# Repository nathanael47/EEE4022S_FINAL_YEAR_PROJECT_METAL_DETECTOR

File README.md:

# EEE4022S_FINAL_YEAR_PROJECT_METAL_DETECTOR
This is the git repository for all code my design and implementation of a metal detector

# PROJECT NAME: DESIGN AND IMPLEMENTATION OF A METAL DETECTOR

# DESCRIPTION:
This is the design and implementation of a metal detector that can detect metals and distinguish if it is ferrous or non ferrous

# INSTALLATION
1. Download the zip version of the repository.
2. Alternatively, pull the repository using the following line;

# USAGE
Prototype:
1. Install arduino and teensyduino
2. Run any of the implementations.
3. Run Metal_Detector.ino

# CREDITS: Done by NATHANAEL GEORGE THOMAS-5/11/2022

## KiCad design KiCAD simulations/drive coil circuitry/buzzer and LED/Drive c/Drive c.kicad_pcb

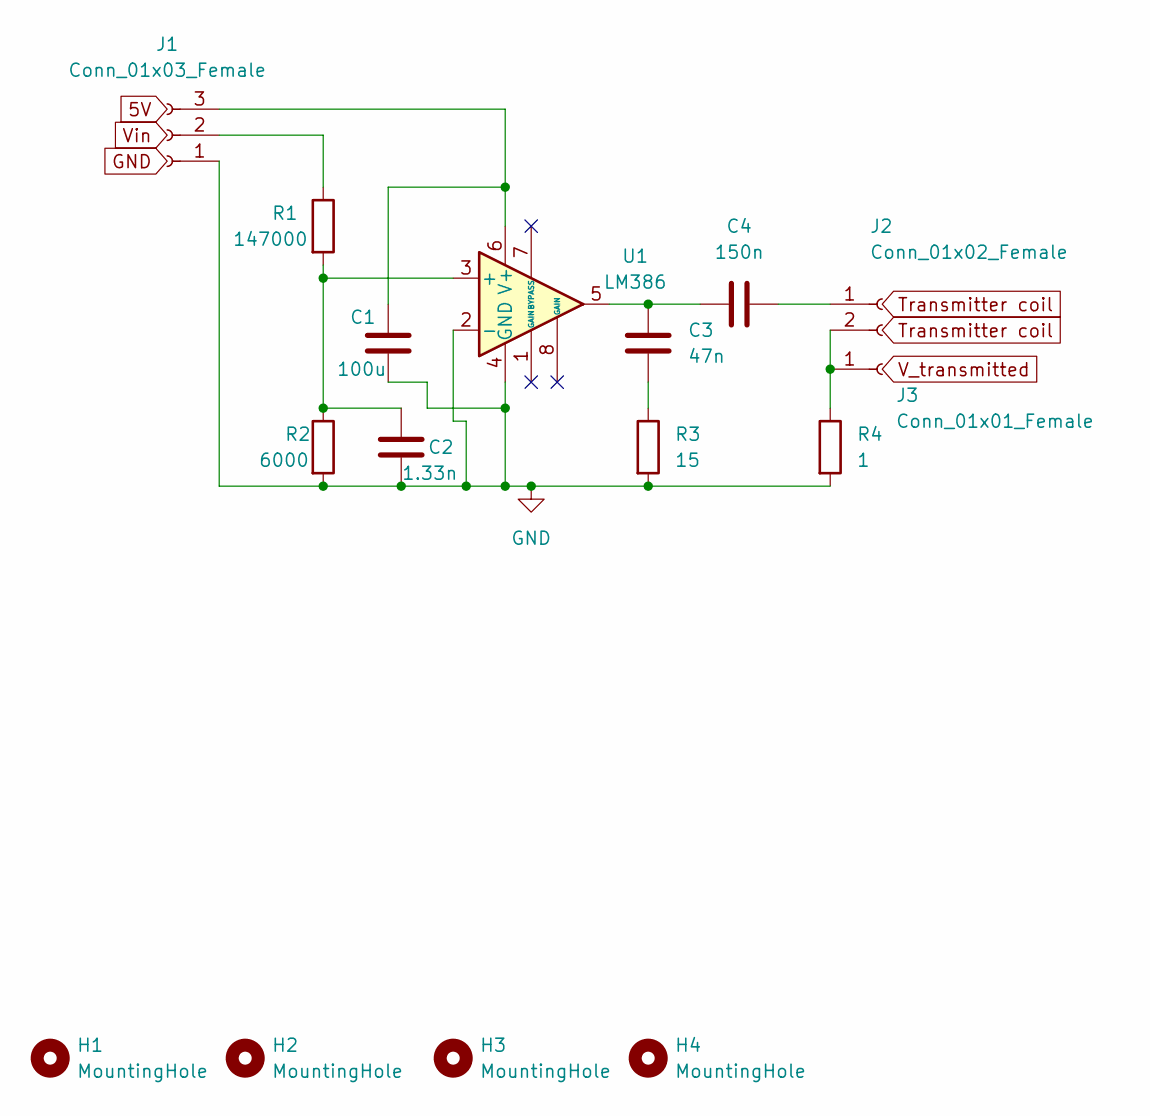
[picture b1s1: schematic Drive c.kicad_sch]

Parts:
C1: 100u; CP_Radial_D7.5mm_P2.50mm
C2: 1.33n; CP_Radial_D7.5mm_P2.50mm
C3: 47n; CP_Radial_D7.5mm_P2.50mm
C4: 150n; CP_Radial_D7.5mm_P2.50mm
H1, H2, H3, H4: MountingHole; MountingHole_2.7mm_M2.5_ISO14580_Pad_TopOnly
J1: Conn_01x03_Female; PinSocket_1x03_P2.54mm_Vertical
J2: Conn_01x02_Female; PinSocket_1x02_P2.54mm_Vertical
J3: Conn_01x01_Female; PinSocket_1x01_P2.54mm_Vertical
R1: 147000; R_Axial_DIN0309_L9.0mm_D3.2mm_P12.70mm_Horizontal
R2: 6000; R_Axial_DIN0309_L9.0mm_D3.2mm_P12.70mm_Horizontal
R3: 15; R_Axial_DIN0309_L9.0mm_D3.2mm_P12.70mm_Horizontal
R4: 1; R_Axial_DIN0309_L9.0mm_D3.2mm_P12.70mm_Horizontal
U1: LM386; DIP-8_W7.62mm

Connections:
GND: C1.2, C2.2, J1.1, R2.2, R3.2, R4.2, U1.2 (-), U1.4 (GND)
unnamed: C1.1, J1.3, U1.6 (V+)
unnamed: C2.1, R1.2, R2.1, U1.3 (+)
unnamed: C3.1, R3.1
unnamed: C3.2, C4.1, U1.5
unnamed: C4.2, J2.1
unnamed: J1.2, R1.1
unnamed: J2.2, J3.1, R4.1

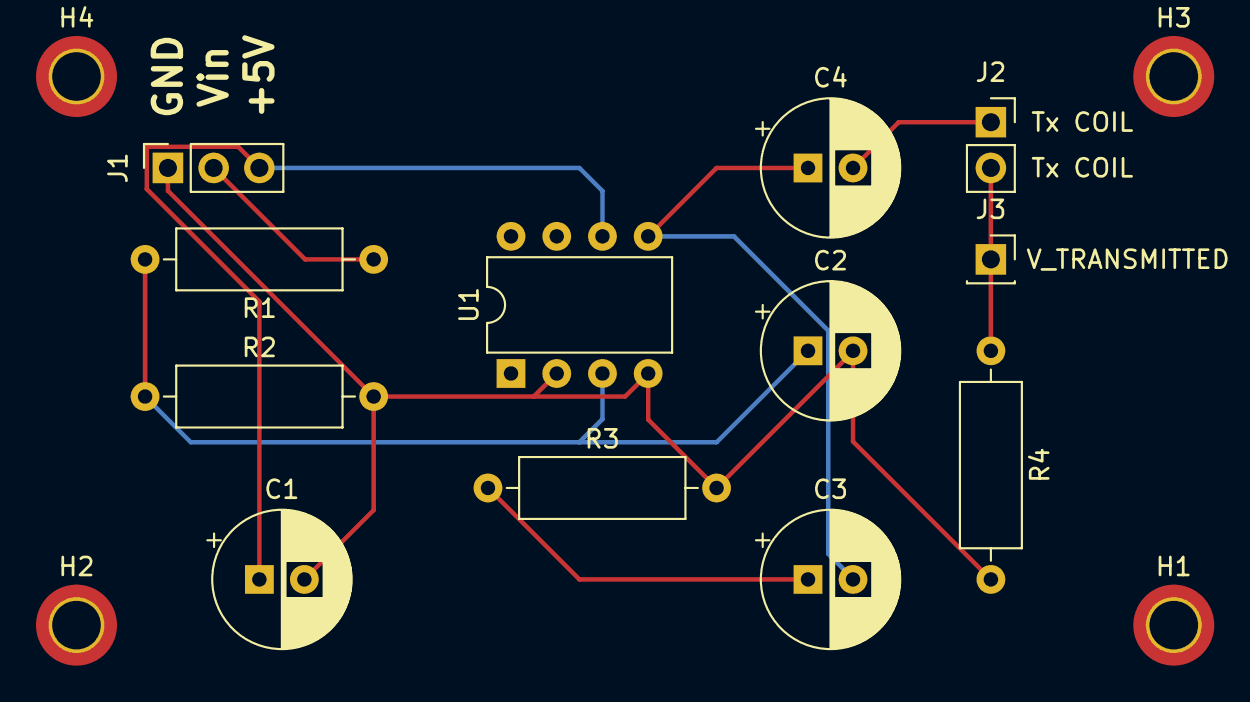
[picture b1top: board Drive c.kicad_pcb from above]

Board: 2 copper layers, 16 parts (0 on the bottom side), 8 nets.

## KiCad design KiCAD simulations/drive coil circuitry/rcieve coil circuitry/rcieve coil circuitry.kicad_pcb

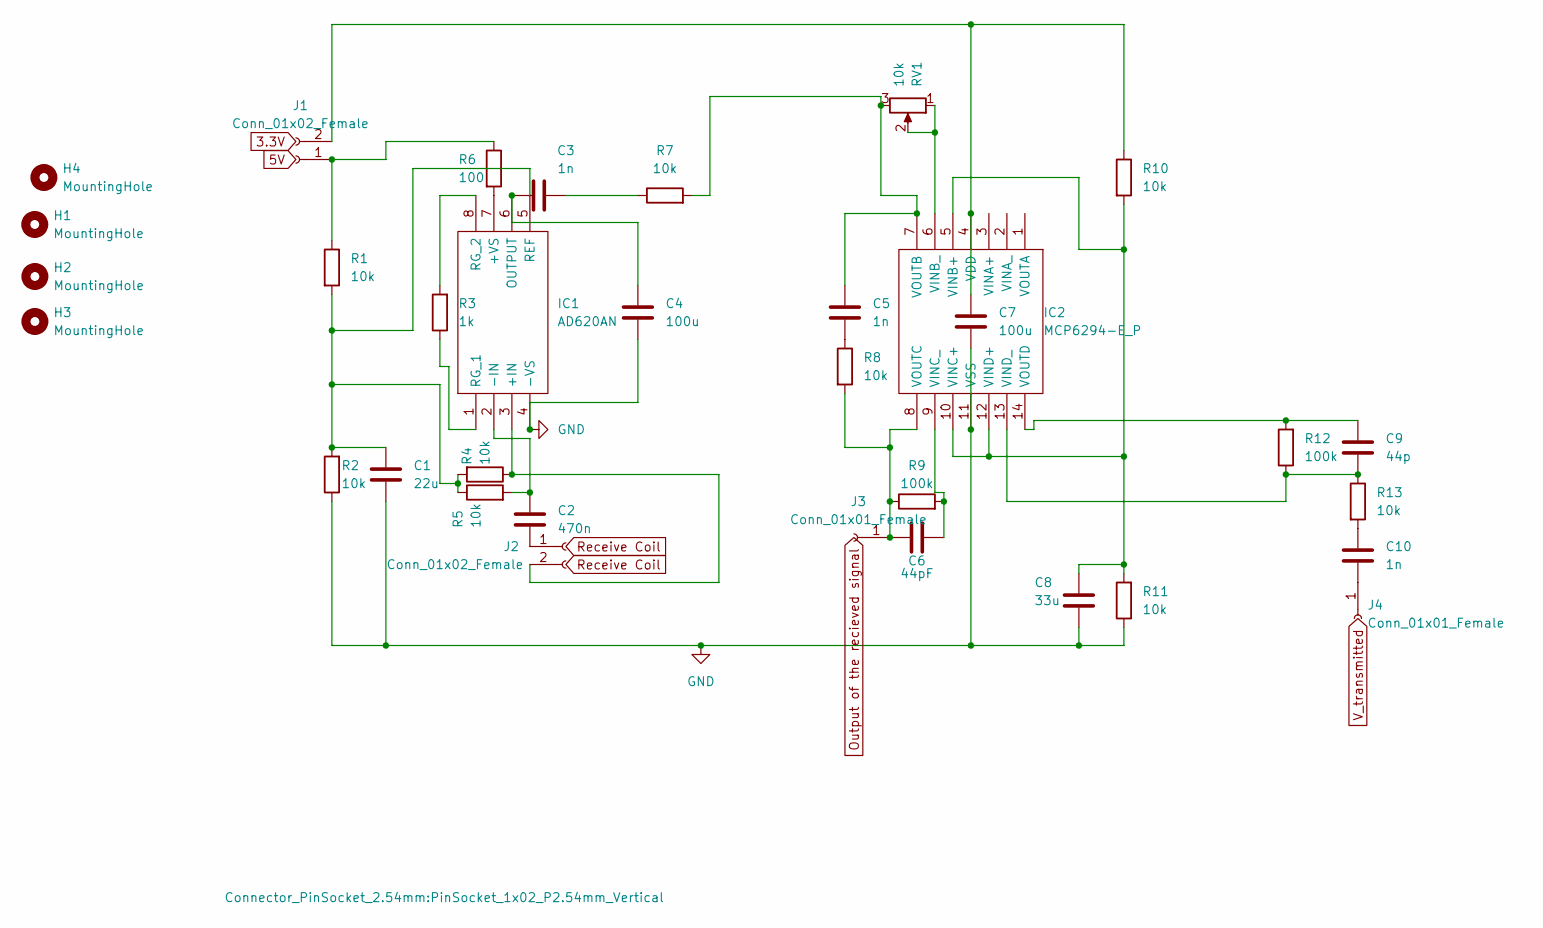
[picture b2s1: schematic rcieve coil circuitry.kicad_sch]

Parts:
C1: 22u; C_Rect_L4.6mm_W3.8mm_P2.50mm_MKS02_FKP02
C2: 470n; C_Rect_L7.0mm_W4.5mm_P5.00mm
C3: 1n; C_Rect_L7.0mm_W6.5mm_P5.00mm
C4: 100u; C_Radial_D10.0mm_H12.5mm_P5.00mm
C5: 1n; C_Rect_L4.6mm_W3.0mm_P2.50mm_MKS02_FKP02
C6: 44pF; C_Rect_L4.6mm_W2.0mm_P2.50mm_MKS02_FKP02
C7: 100u; C_Radial_D6.3mm_H5.0mm_P2.50mm
C8: 33u; C_Radial_D6.3mm_H5.0mm_P2.50mm
C9: 44p; C_Rect_L4.0mm_W2.5mm_P2.50mm
C10: 1n; C_Rect_L4.0mm_W2.5mm_P2.50mm
H1, H2, H3, H4: MountingHole; MountingHole_2.2mm_M2
IC1: AD620AN; DIP-8_W7.62mm_LongPads; Manufacturer_Part_Number AD620AN; Mouser Part Number 584-AD620AN
IC2: MCP6294-E_P; DIP-14_W7.62mm_LongPads; Manufacturer_Part_Number MCP6294-E/P; Mouser Part Number 579-MCP6294-E/P
J1, J2: Conn_01x02_Female; PinSocket_1x02_P2.54mm_Vertical
J3, J4: Conn_01x01_Female; PinSocket_1x01_P2.54mm_Vertical
R1, R2: 10k; R_Axial_DIN0309_L9.0mm_D3.2mm_P5.08mm_Vertical
R3: 1k; R_Axial_DIN0309_L9.0mm_D3.2mm_P5.08mm_Vertical
R4, R5, R7, R8, R10, R11: 10k; R_Axial_DIN0614_L14.3mm_D5.7mm_P15.24mm_Horizontal
R6: 100; R_Axial_DIN0614_L14.3mm_D5.7mm_P15.24mm_Horizontal
R9: 100k; R_Axial_DIN0614_L14.3mm_D5.7mm_P15.24mm_Horizontal
R12: 100k; R_Axial_DIN0414_L11.9mm_D4.5mm_P15.24mm_Horizontal
R13: 10k; R_Axial_DIN0414_L11.9mm_D4.5mm_P15.24mm_Horizontal
RV1: 10k; Potentiometer_Alps_RK09K_Single_Vertical

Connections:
GND: C1.2, C4.2, C7.2, C8.2, IC1.4 (-VS), IC2.11 (VSS), R2.1, R11.1
unnamed: C1.1, IC1.5 (REF), R1.2, R2.2, R4.2, R5.1
unnamed: C2.1, IC1.2 (-IN), R5.2
unnamed: C2.2, J2.1
unnamed: C3.1, C4.1, IC1.6 (OUTPUT)
unnamed: C3.2, R7.1
unnamed: C5.1, IC2.7 (VOUTB), R7.2, RV1.3
unnamed: C5.2, R8.1
unnamed: C6.1, IC2.8 (VOUTC), J3.1, R8.2, R9.1
unnamed: C6.2, IC2.9 (VINC_), R9.2
unnamed: C8.1, IC2.5 (VINB+), IC2.10 (VINC+), IC2.12 (VIND+), R10.2, R11.2
unnamed: C9.1, IC2.14 (VOUTD), R12.2
unnamed: C9.2, IC2.13 (VIND_), R12.1, R13.1
unnamed: C10.1, R13.2
unnamed: C10.2, J4.1
unnamed: IC1.1 (RG_1), R3.1
unnamed: IC1.3 (+IN), J2.2, R4.1
unnamed: IC1.7 (+VS), R6.2
unnamed: IC1.8 (RG_2), R3.2
unnamed: IC2.6 (VINB_), RV1.1, RV1.2
unnamed: J1.1, R1.1, R6.1
unnamed: C7.1, IC2.4 (VDD), J1.2, R10.1

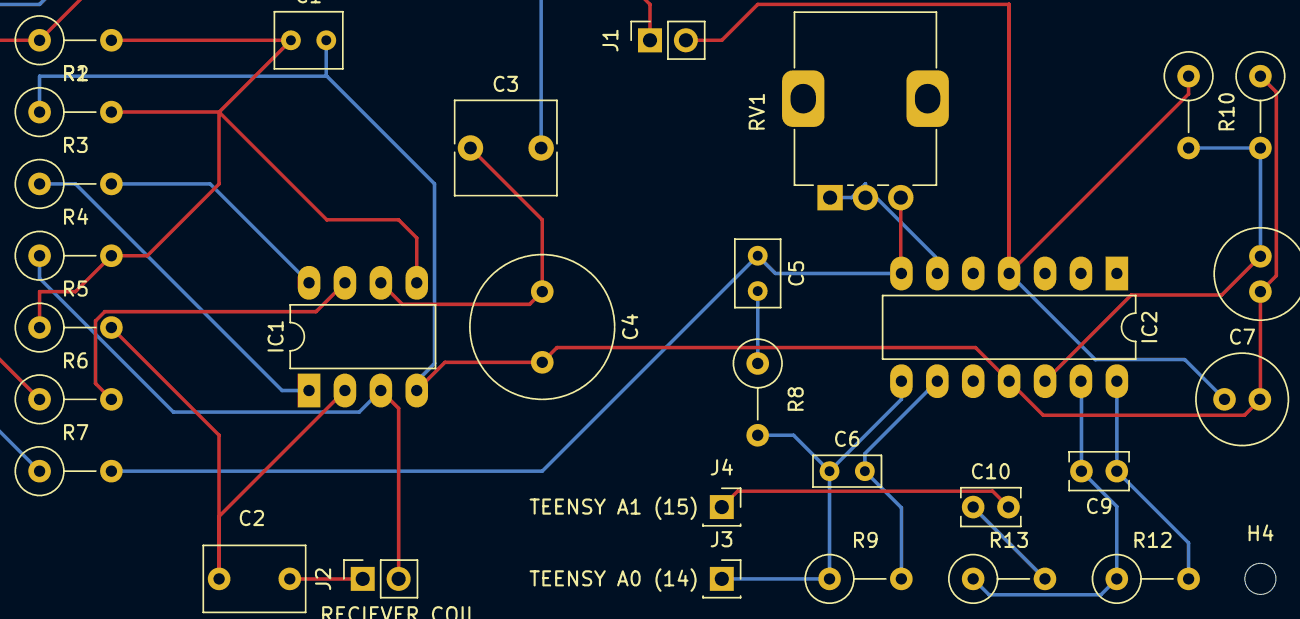
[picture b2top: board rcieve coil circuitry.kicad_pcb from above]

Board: 2 copper layers, 34 parts (0 on the bottom side), 22 nets.

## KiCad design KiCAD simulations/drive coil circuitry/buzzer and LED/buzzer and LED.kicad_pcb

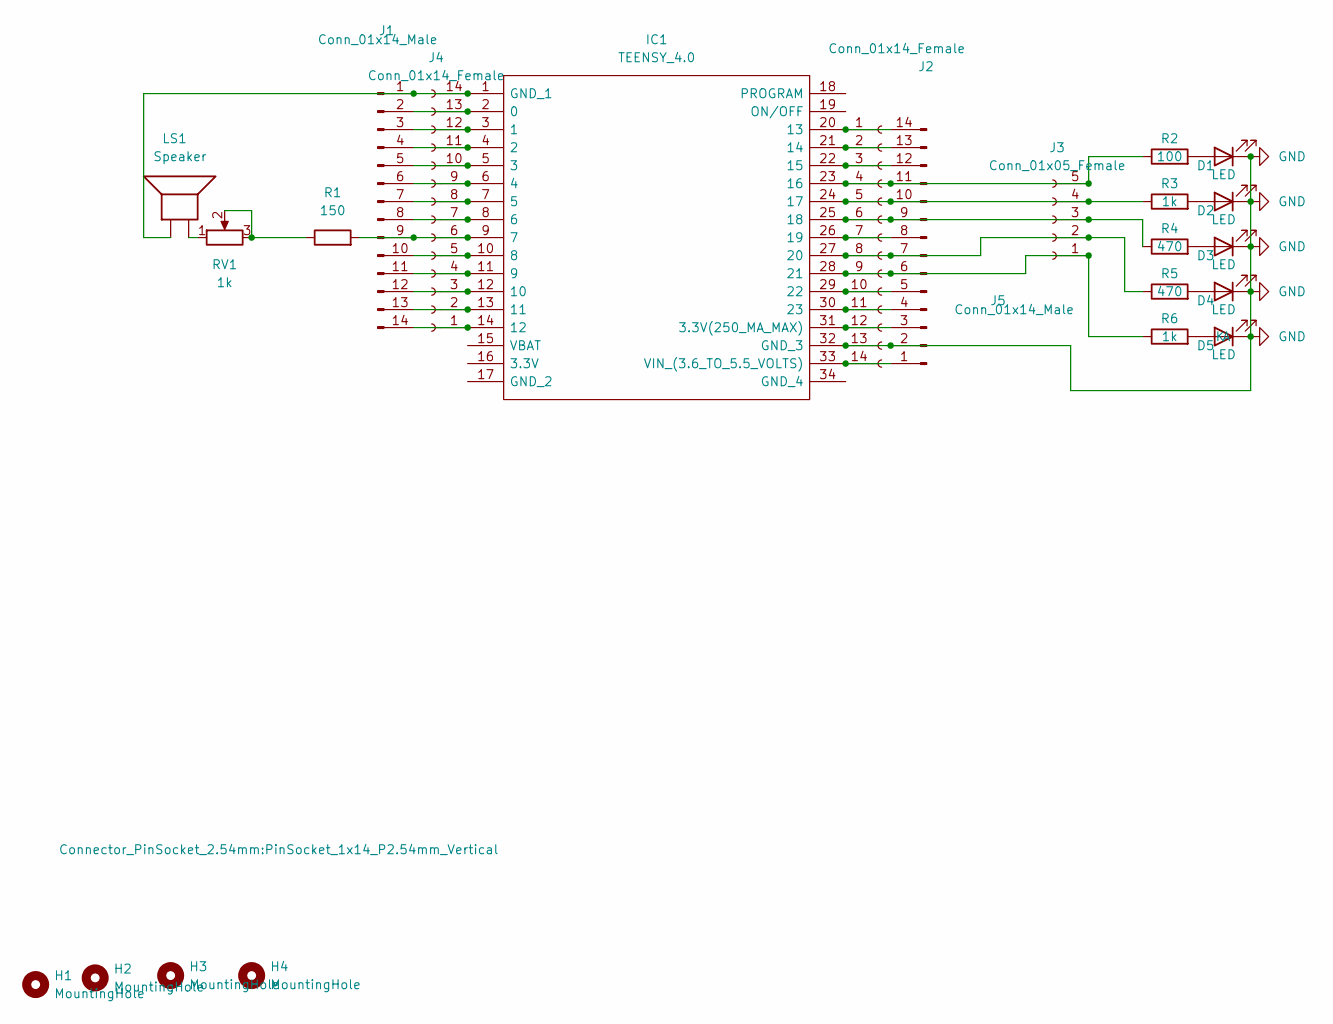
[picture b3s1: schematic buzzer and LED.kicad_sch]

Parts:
D1, D2, D3, D4: LED; LED_D3.0mm_Clear
D5: LED; LED_D3.0mm
H1, H2, H3, H4: MountingHole; MountingHole_2.1mm
IC1: TEENSY_4.0; TEENSY40; Manufacturer_Part_Number TEENSY 4.0
J1, J2: Conn_01x14_Male; PinHeader_1x14_P2.54mm_Vertical
J3: Conn_01x05_Female; PinSocket_1x05_P1.27mm_Vertical
J4, J5: Conn_01x14_Female; PinSocket_1x14_P2.54mm_Vertical
LS1: Speaker; Buzzer_12x9.5RM7.6
R1: 150; R_Axial_DIN0207_L6.3mm_D2.5mm_P5.08mm_Vertical
R2: 100; R_Axial_DIN0207_L6.3mm_D2.5mm_P5.08mm_Vertical
R3, R6: 1k; R_Axial_DIN0207_L6.3mm_D2.5mm_P5.08mm_Vertical
R4, R5: 470; R_Axial_DIN0207_L6.3mm_D2.5mm_P5.08mm_Vertical
RV1: 1k; Potentiometer_Alps_RK163_Single_Horizontal

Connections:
unnamed: D1.2 (A), R2.2
unnamed: D2.2 (A), R3.2
unnamed: D3.2 (A), R4.2
unnamed: D4.2 (A), R5.2
unnamed: D5.2 (A), R6.2
unnamed: IC1.1 (GND_1), J1.1, J4.14, LS1.1
unnamed: IC1.2 (0), J1.2, J4.13
unnamed: IC1.3 (1), J1.3, J4.12
unnamed: IC1.4 (2), J1.4, J4.11
unnamed: IC1.5 (3), J1.5, J4.10
unnamed: IC1.6 (4), J1.6, J4.9
unnamed: IC1.7 (5), J1.7, J4.8
unnamed: IC1.8 (6), J1.8, J4.7
unnamed: IC1.9 (7), J1.9, J4.6, R1.2
unnamed: IC1.10 (8), J1.10, J4.5
unnamed: IC1.11 (9), J1.11, J4.4
unnamed: IC1.12 (10), J1.12, J4.3
unnamed: IC1.13 (11), J1.13, J4.2
unnamed: IC1.14 (12), J1.14, J4.1
unnamed: IC1.20 (13), J2.14, J5.1
unnamed: IC1.21 (14), J2.13, J5.2
unnamed: IC1.22 (15), J2.12, J5.3
unnamed: IC1.23 (16), J2.11, J3.5, J5.4, R2.1
unnamed: IC1.24 (17), J2.10, J3.4, J5.5, R3.1
unnamed: IC1.25 (18), J2.9, J3.3, J5.6, R4.1
unnamed: IC1.26 (19), J2.8, J5.7
unnamed: IC1.27 (20), J2.7, J3.2, J5.8, R5.1
unnamed: IC1.28 (21), J2.6, J3.1, J5.9, R6.1
unnamed: IC1.29 (22), J2.5, J5.10
unnamed: IC1.30 (23), J2.4, J5.11
unnamed: IC1.31 (3.3V(250_MA_MAX)), J2.3, J5.12
unnamed: IC1.33 (VIN_(3.6_TO_5.5_VOLTS)), J2.1, J5.14
unnamed: LS1.2, RV1.1
unnamed: R1.1, RV1.2, RV1.3

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
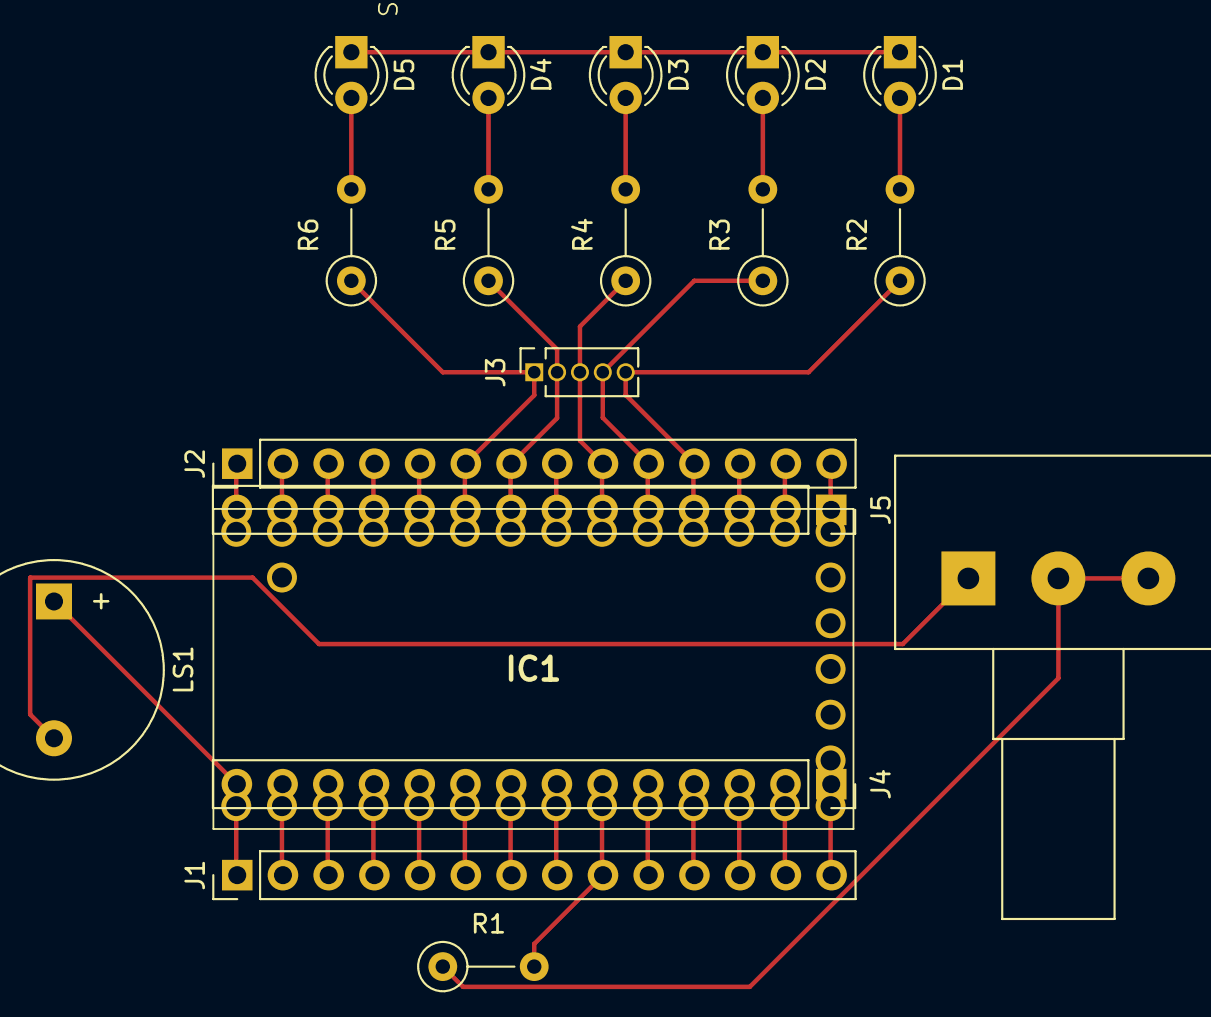
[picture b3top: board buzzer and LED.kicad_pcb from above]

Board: 2 copper layers, 23 parts (0 on the bottom side), 36 nets.
